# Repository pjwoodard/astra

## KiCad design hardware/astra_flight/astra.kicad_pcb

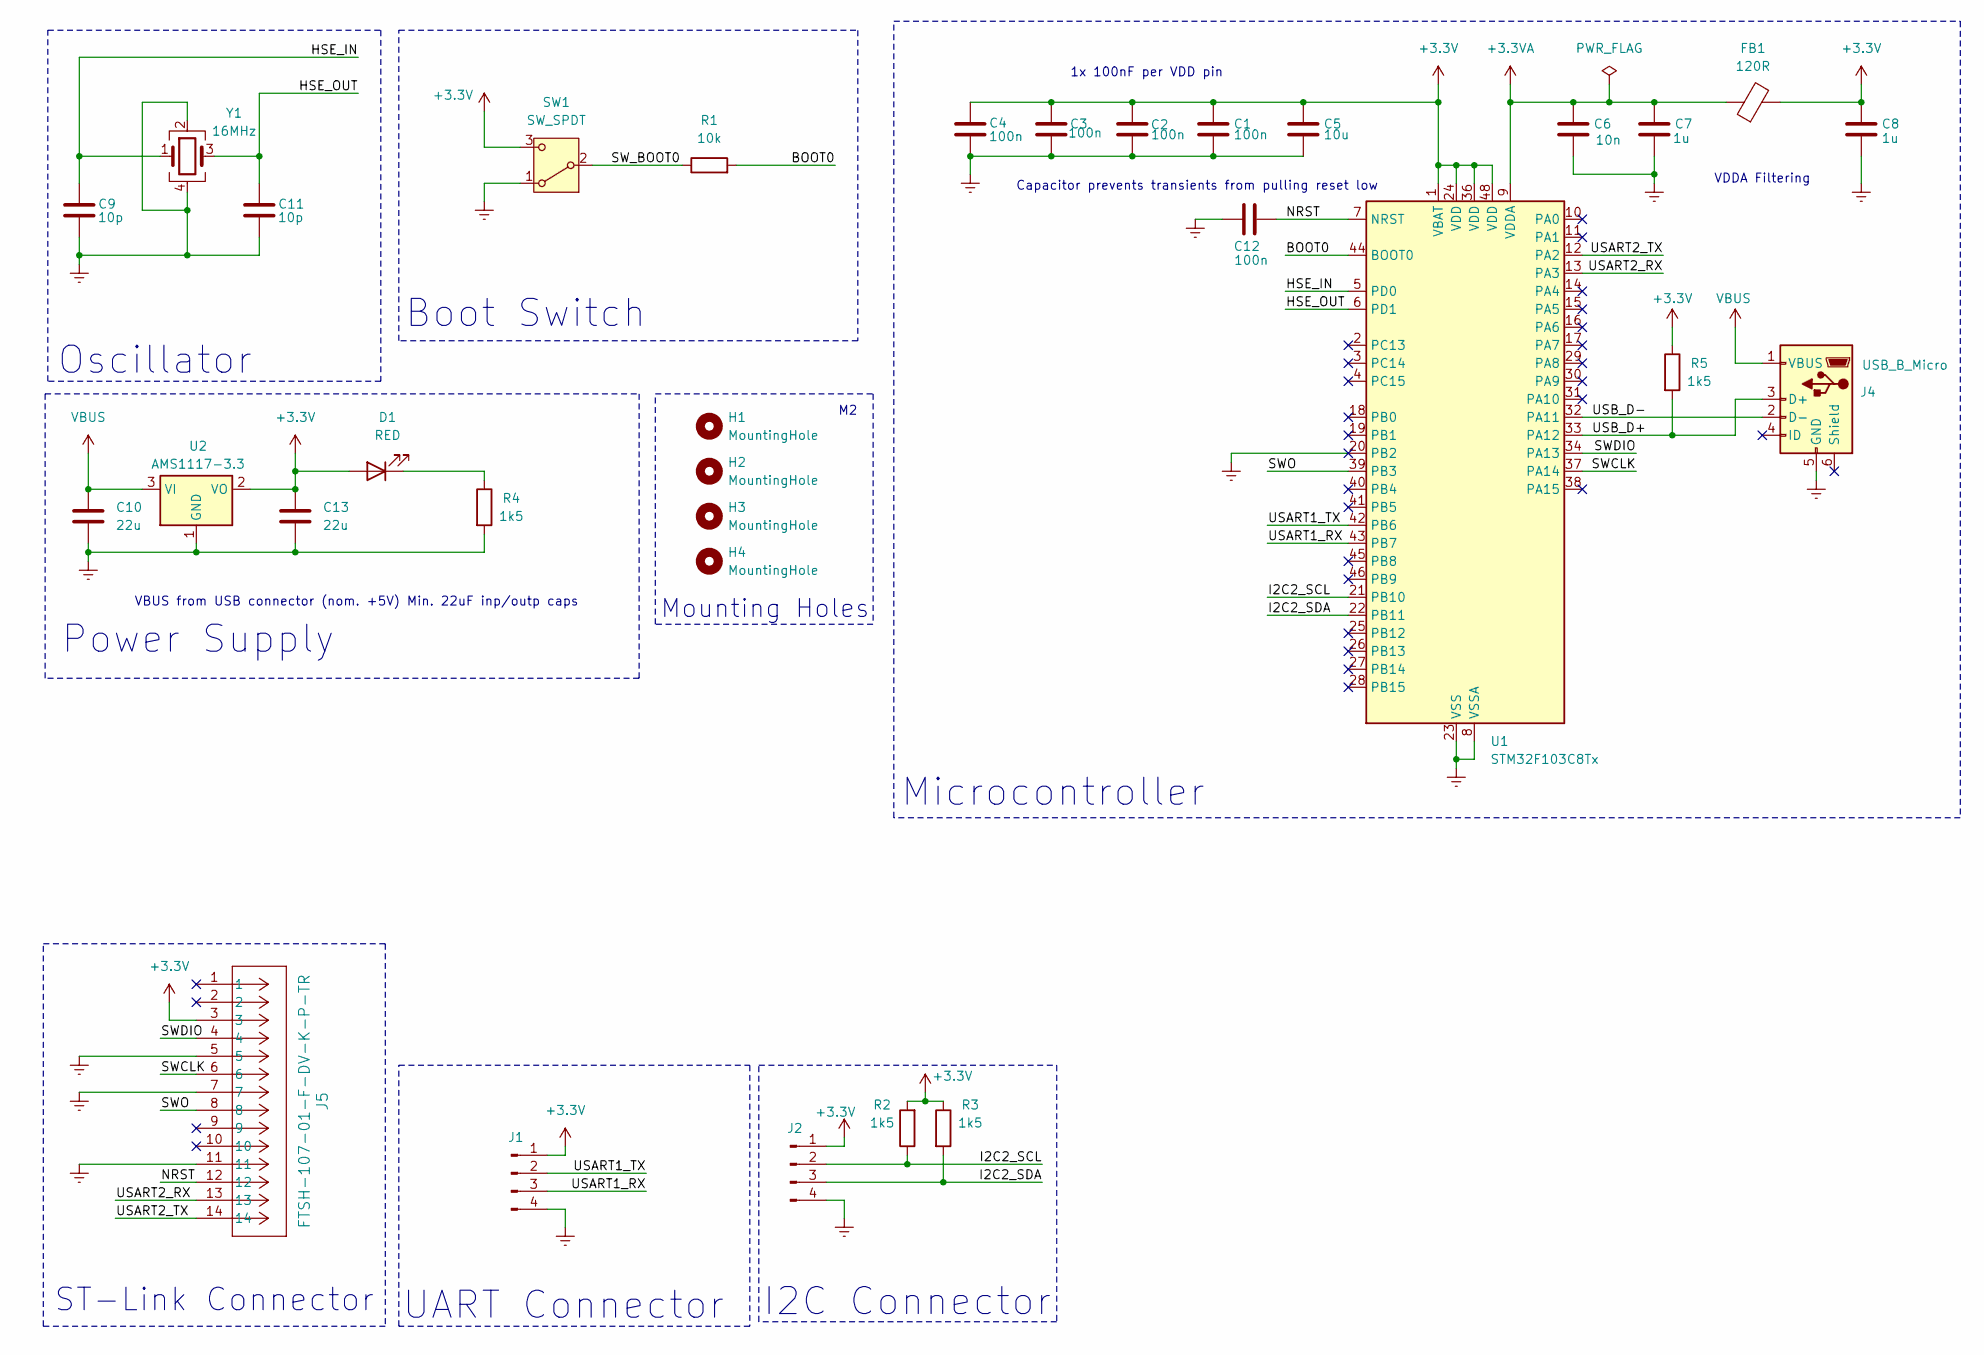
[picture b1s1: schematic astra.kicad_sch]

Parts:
C1, C2, C3, C4, C12: 100n; C_0402_1005Metric
C5: 10u; C_0603_1608Metric
C6: 10n; C_0402_1005Metric
C7, C8: 1u; C_0402_1005Metric
C9, C11: 10p; C_0402_1005Metric
C10, C13: 22u; C_0805_2012Metric
D1: RED; LED_0603_1608Metric
FB1: 120R; L_0603_1608Metric
H1, H2, H3, H4: MountingHole; MountingHole_2.2mm_M2
J1, J2: Conn_01x04_Pin; PinHeader_1x04_P2.54mm_Vertical
J4: USB_B_Micro; USB_Micro-B_Wuerth_629105150521
J5: FTSH-107-01-F-DV-K-P-TR; SAMTEC_FTSH-107-01-F-DV-K-P-TR
R1: 10k; R_0402_1005Metric
R2, R3, R4, R5: 1k5; R_0402_1005Metric
SW1: SW_SPDT; SW_SPDT_PCM12
U1: STM32F103C8Tx; LQFP-48_7x7mm_P0.5mm
U2: AMS1117-3.3; SOT-223-3_TabPin2
Y1: 16MHz; Crystal_SMD_3225-4Pin_3.2x2.5mm

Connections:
+3.3V: C1.1, C2.1, C3.1, C4.1, C5.1, C8.1, C13.1, D1.2 (A), FB1.2, J1.1, J2.1, J5.3, R2.2, R3.1, R5.1, SW1.3 (C), U1.1 (VBAT), U1.24 (VDD), U1.36 (VDD), U1.48 (VDD), U2.2 (VO)
+3.3VA: C6.1, C7.1, FB1.1, U1.9 (VDDA)
/BOOT0: R1.2, U1.44 (BOOT0)
/HSE_IN: C9.1, U1.5 (PD0), Y1.1
/HSE_OUT: C11.1, U1.6 (PD1), Y1.3
/I2C2_SCL: J2.2, R2.1, U1.21 (PB10)
/I2C2_SDA: J2.3, R3.2, U1.22 (PB11)
/NRST: C12.1, J5.12, U1.7 (NRST)
/SWCLK: J5.6, U1.37 (PA14)
/SWDIO: J5.4, U1.34 (PA13)
/SWO: J5.8, U1.39 (PB3)
/SW_BOOT0: R1.1, SW1.2 (B)
/USART1_RX: J1.3, U1.43 (PB7)
/USART1_TX: J1.2, U1.42 (PB6)
/USART2_RX: J5.13, U1.13 (PA3)
/USART2_TX: J5.14, U1.12 (PA2)
/USB_D+: J4.3 (D+), R5.2, U1.33 (PA12)
/USB_D-: J4.2 (D-), U1.32 (PA11)
Earth: C1.2, C2.2, C3.2, C4.2, C5.2, C6.2, C7.2, C8.2, C9.2, C10.2, C11.2, C12.2, C13.2, J1.4, J2.4, J4.5 (GND), J5.5, J5.7, J5.11, R4.2, SW1.1 (A), U1.8 (VSSA), U1.20 (PB2), U1.23 (VSS), U1.35 (VSS), U1.47 (VSS), U2.1 (GND), Y1.2, Y1.4
unnamed: D1.1 (K), R4.1
VBUS: C10.1, J4.1 (VBUS), U2.3 (VI)

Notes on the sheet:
VBUS from USB connector (nom. +5V) Min. 22uF inp/outp caps
1x 100nF per VDD pin
Boot Switch
VDDA Filtering
Power Supply
Capacitor prevents transients from pulling reset low
UART Connector
Mounting Holes
Oscillator
Microcontroller
I2C Connector
ST-Link Connector

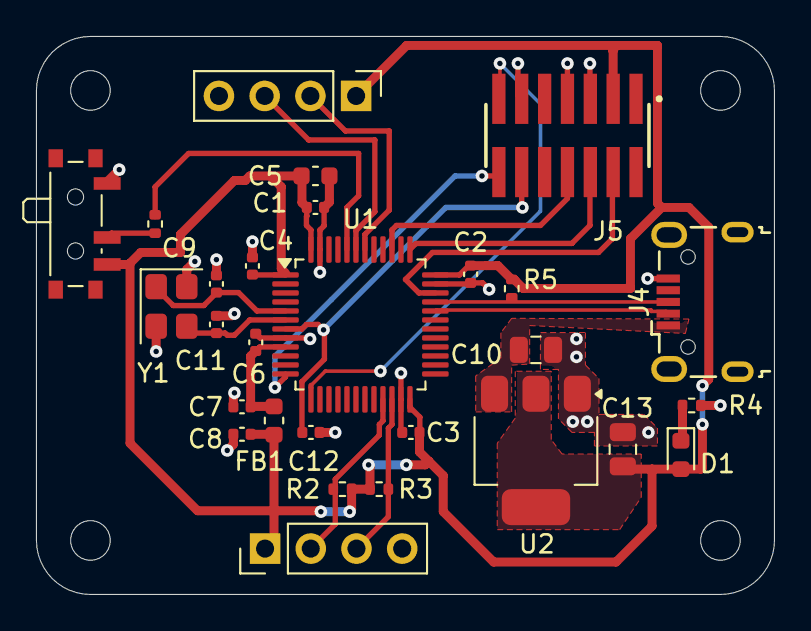
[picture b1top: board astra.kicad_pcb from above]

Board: 2 copper layers, 41.0 x 31.0 mm, 32 parts (0 on the bottom side), 21 nets.

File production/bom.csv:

Designator,Footprint,Quantity,Value,LCSC Part #
"C1, C12, C2, C3, C4",0402,5,100n,
"C10, C13",0805,2,22u,
"C11, C9",0402,2,10p,
C5,0603,1,10u,
C6,0402,1,10n,
"C7, C8",0402,2,1u,
D1,0603,1,RED,
FB1,0603,1,120R,
"J1, J2",PinHeader_1x04_P2.54mm_Vertical,2,Conn_01x04_Pin,
J4,USB_Micro-B_Wuerth_629105150521,1,USB_B_Micro,
J5,SAMTEC_FTSH-107-01-F-DV-K-P-TR,1,FTSH-107-01-F-DV-K-P-TR,
R1,0402,1,10k,
"R2, R3, R4, R5",0402,4,1k5,
SW1,SW_SPDT_PCM12,1,SW_SPDT,
U1,LQFP-48_7x7mm_P0.5mm,1,STM32F103C8Tx,
U2,SOT-223-3_TabPin2,1,AMS1117-3.3,
Y1,Crystal_SMD_3225-4Pin_3.2x2.5mm,1,16MHz,

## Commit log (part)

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2026-02-02 move hardware into a hw folder
2026-03-01 astra software
2026-03-01 Support multiple hardware easily
2026-03-01 Add gitignore
2026-03-16 Dont save backups to git
2026-03-16 Move FC to astra_flight directory
2026-06-22 Astra Radio
2026-06-22 Remove checked in backups
2026-06-23 Add 5V -> 3.3V LDO symbols / footprint
2026-06-23 Commit Footprint library
2026-06-23 Add LD39100PU33RY 3D model
2026-06-24 Lots of new stuff, but lost some stuff :-)
2026-06-24 Alsmot there
